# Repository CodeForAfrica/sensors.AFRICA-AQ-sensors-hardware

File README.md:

# AQ-Sensors-Hardware-Design

These are the design files for the https://sensors.africa/ by https://codeforafrica.org/ AQ kits PCB.

## Tools used

* Autodesk Eagle

* Fusion360

## sensors.AFRICA Stack

1. Firmware - https://github.com/CodeForAfrica/sensors.AFRICA-AQ-sensors-software

2. API - https://github.com/CodeForAfricaLabs/sensors.AFRICA-AQ-api

3. Map - https://github.com/CodeForAfrica/sensors.AFRICA-AQ-map-v2

## Documentation

The Documentation is under development.

## Attribution;

We used the following reference designs in our final design files. We are thankful to the owners for making them open-source.

1. https://github.com/adafruit/Adafruit-FONA-808-Breakout-PCB

2. https://github.com/SeaSlugLabs/Wisol-WSSFM10R2-Sigfox-Breakout/tree/master/Hardware

3. https://github.com/lupyuen/Wisol-WSSFM10R-Sigfox-Breakout

## License

GNU General Public License v3.0

sensors.AFRICA is a citizen-science focused project by Code for Africa that seeks to address data gaps by providing low cost sensors, which people can use to measure and monitor the quality of the air, water, and environment in their communities. This web app seeks to be the public portal through which most users would discover and explore the data and intiative.

Copyright (C) 2019 Code for Africa

This program is free software: you can redistribute it and/or modify
it under the terms of the GNU General Public License as published by
the Free Software Foundation, either version 3 of the License, or
(at your option) any later version.

This program is distributed in the hope that it will be useful,
but WITHOUT ANY WARRANTY; without even the implied warranty of
MERCHANTABILITY or FITNESS FOR A PARTICULAR PURPOSE. See the
GNU General Public License for more details.

You should have received a copy of the GNU General Public License
along with this program. If not, see <https://www.gnu.org/licenses/>

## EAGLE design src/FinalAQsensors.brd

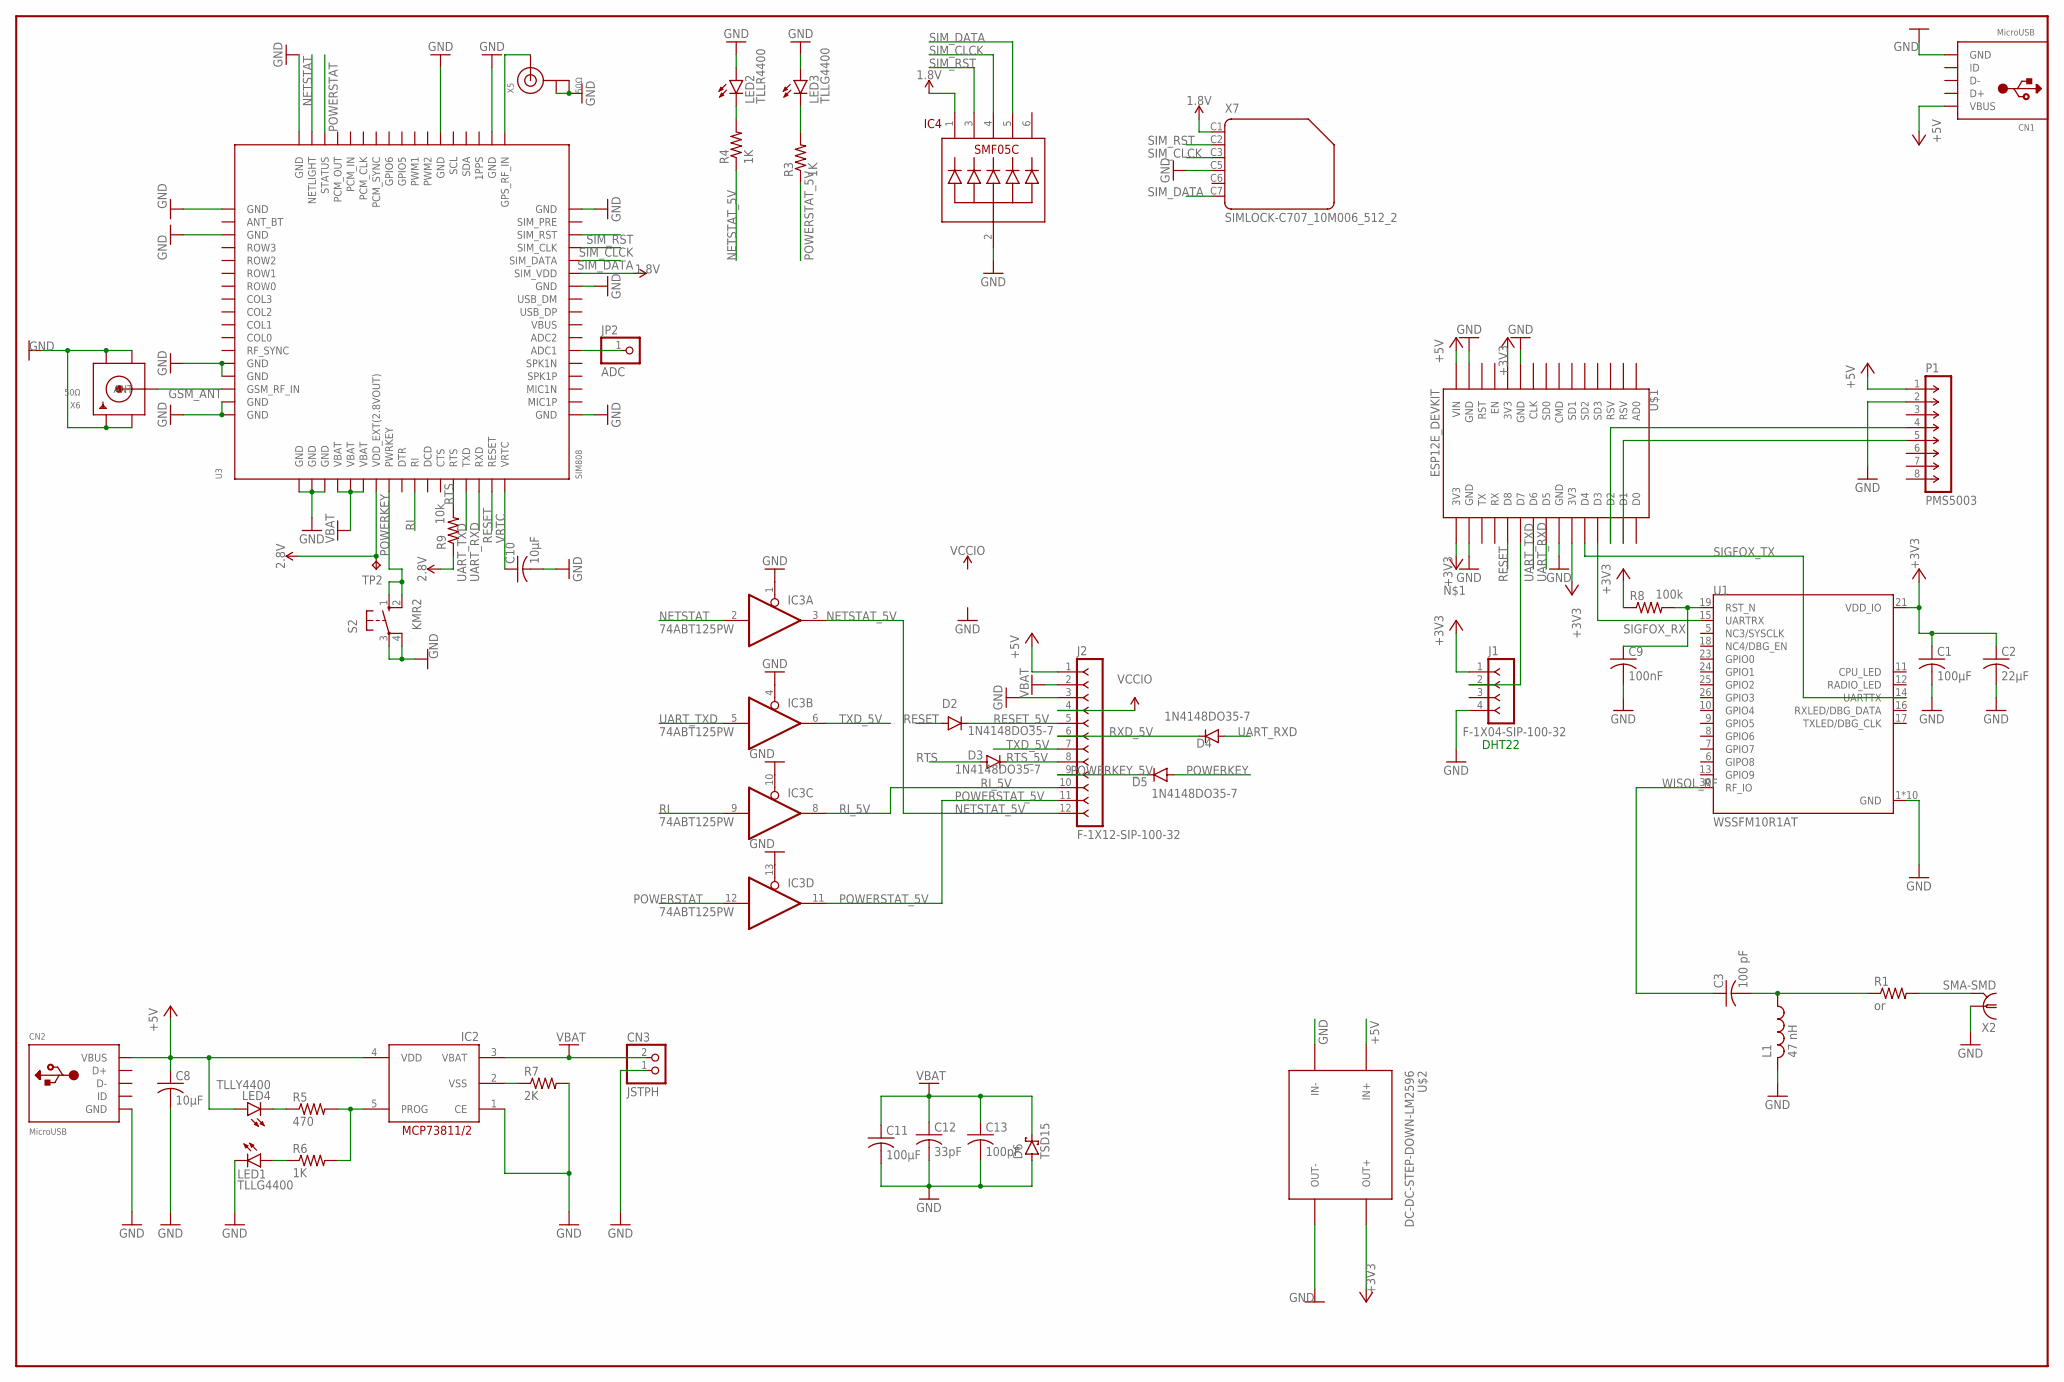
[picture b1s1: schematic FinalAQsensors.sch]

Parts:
C1: 100μF; C0201
C2: 22μF; C0201
C3: 100 pF; C0201
C8: 10μF; C025-025X050
C9: 100nF; C025-025X050
C10: 10μF; C0402
C11: 100μF; C0402
C12: 33pF; C0402
C13: 100pF; C0402
CN1, CN2: MicroUSB; USB-MINIB
CN3: JSTPH; JST-PH-2-SMT
D2, D3, D4, D5: 1N4148DO35-7; DO35-7
D6: TSD15; CB429-15
IC2: MCP73811/2; SOT23-5L
IC3: 74ABT125PW; TSSOP14
IC4: SMF05C; SC-70-6
J1: F-1X04-SIP-100-32; SIP-100-04-32
J2: F-1X12-SIP-100-32; SIP-100-12-32
JP2: ADC; 1X01M
L1: 47 nH; 0204/7
LED1, LED3: TLLG4400; LED3MM
LED2: TLLR4400; LED3MM
LED4: TLLY4400; LED3MM
P1: PMS5003; SIP-100-08-40
R1: or; 0204/5
R3, R4, R6: 1K; 0204/5
R5: 470; 0204/5
R7: 2K; 0204/5
R8: 100k; 0204/7
R9: 10k; 0204/5
S2: KMR2; B3F/40XX
TP2: TPTP10R; TP10R
U1: WSSFM10R1AT; XCVR_WSSFM10R1AT
U3: SIM808; SIM900_SMT
U$1: ESP12E_DEVKIT
U$2: DC-DC-STEP-DOWN-LM2596
X2: SMA-SMD
X5: 50Ω; U.FL
X6: 50Ω; SMA_EDGELAUNCH_UFL
X7: SIMLOCK-C707_10M006_512_2; C707_10M006_512_2

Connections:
1.8V: IC4.1, U3.P$29 (SIM_VDD), X7.C1 (1)
2.8V: R9.1, TP2.TP, U3.P$7 (VDD_EXT(2.8VOUT))
+3V3: C1.1, C2.1, J1.1, R8.1, U1.21 (VDD_IO), U$1.3V3@0 (3V3), U$1.3V3@1 (3V3), U$1.3V3@2 (3V3), U$2.OUT+
+5V: C8.1, CN1.VBUS, CN2.VBUS, IC2.4 (VDD), J2.1, LED4.A, P1.1, U$1.VIN, U$2.IN+
GND: C1.2, C2.2, C8.2, C9.2, C10.2, C11.2, C12.2, C13.2, CN1.GND, CN2.GND, CN3.1 (2), D6.A, IC2.1 (CE), IC3.1 (OE), IC3.4 (OE), IC3.7 (GND), IC3.10 (OE), IC3.13 (OE), IC4.2, J1.4, J2.3, L1.2, LED1.K (C), LED2.A, LED3.A, P1.2, R7.2, S2.3, S2.4 (P1), U1.1 (GND), U1.2 (GND), U1.3 (GND), U1.4 (GND), U1.20 (GND), U1.22 (GND), U1.27 (GND), U1.28 (GND), U1.29 (GND), U1.31 (GND), U3.P$1 (GND), U3.P$2 (GND), U3.P$3 (GND), U3.P$18 (GND), U3.P$28 (GND), U3.P$34 (GND), U3.P$36 (GND), U3.P$40 (GND), U3.P$51 (GND), U3.P$52 (GND), U3.P$54 (GND), U3.P$64 (GND), U3.P$65 (GND), U3.P$67 (GND), U3.P$68 (GND), U$1.GND@0 (GND), U$1.GND@1 (GND), U$1.GND@2 (GND), U$1.GND@3 (GND), U$2.IN-, U$2.OUT-, X2.1, X5.1 (GND), X5.2 (GND), X6.GND@1 (GND1), X6.GND@2 (GND2), X6.GND@3 (GND3), X6.GND@4 (GND4), X7.C5 (4)
GSM_ANT: U3.P$66 (GSM_RF_IN), X6.P (ANT)
unnamed: J1.2, U$1.D7
unnamed: C9.1, R8.2, U1.19 (RST_N)
unnamed: P1.4, U$1.D2
unnamed: P1.5, U$1.D1
unnamed: C3.2, L1.1, R1.1
unnamed: U3.P$35 (GPS_RF_IN), X5.3 (SIGNAL)
unnamed: R1.2, X2.2@1 (2), X2.2@2 (2), X2.2@3 (2), X2.2@4 (2), X2.2@5 (2), X2.2@6 (2)
unnamed: JP2.1, U3.P$23 (ADC1)
unnamed: LED2.K (C), R4.2
unnamed: LED3.K (C), R3.2
unnamed: LED4.K (C), R5.1
unnamed: IC2.5 (PROG), R5.2, R6.2
unnamed: LED1.A, R6.1
NETSTAT: IC3.2 (I), U3.P$50 (NETLIGHT)
NETSTAT_5V: IC3.3 (O), J2.12, R4.1
POWERKEY: D5.A, S2.1 (S), S2.2 (S1), U3.P$8 (PWRKEY)
POWERKEY_5V: D5.C, J2.9
POWERSTAT: IC3.12 (I), U3.P$49 (STATUS)
POWERSTAT_5V: IC3.11 (O), J2.11, R3.1
RESET: D2.A, U3.P$16 (RESET), U$1.D8
RESET_5V: D2.C, J2.5
RI: IC3.9 (I), U3.P$10 (RI)
RI_5V: IC3.8 (O), J2.10
RTS: D3.A, R9.2, U3.P$13 (RTS)
RTS_5V: D3.C, J2.8
RXD_5V: D4.C, J2.6
SIGFOX_RX: U1.15 (UARTRX), U$1.D3
SIGFOX_TX: U1.14 (UARTTX), U$1.D4
SIM_CLCK: IC4.4, U3.P$31 (SIM_CLK), X7.C3 (3)
SIM_DATA: IC4.5, U3.P$30 (SIM_DATA), X7.C7 (6)
SIM_RST: IC4.3, U3.P$32 (SIM_RST), X7.C2 (2)
TXD_5V: IC3.6 (O), J2.7
UART_RXD: D4.A, U3.P$15 (RXD), U$1.D5
UART_TXD: IC3.5 (I), U3.P$14 (TXD), U$1.D6
VBAT: C11.1, C12.1, C13.1, CN3.2 (1), D6.C, IC2.3 (VBAT), J2.2, U3.P$4 (VBAT), U3.P$5 (VBAT), U3.P$6 (VBAT)
VBUS: U3.P$25 (VBUS)
VCC: IC3.14 (VCC)
VCCIO: J2.4
VRTC: C10.1, U3.P$17 (VRTC)
VSS: IC2.2 (VSS), R7.1
WISOL_RF: C3.1, U1.30 (RF_IO)

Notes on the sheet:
DHT22

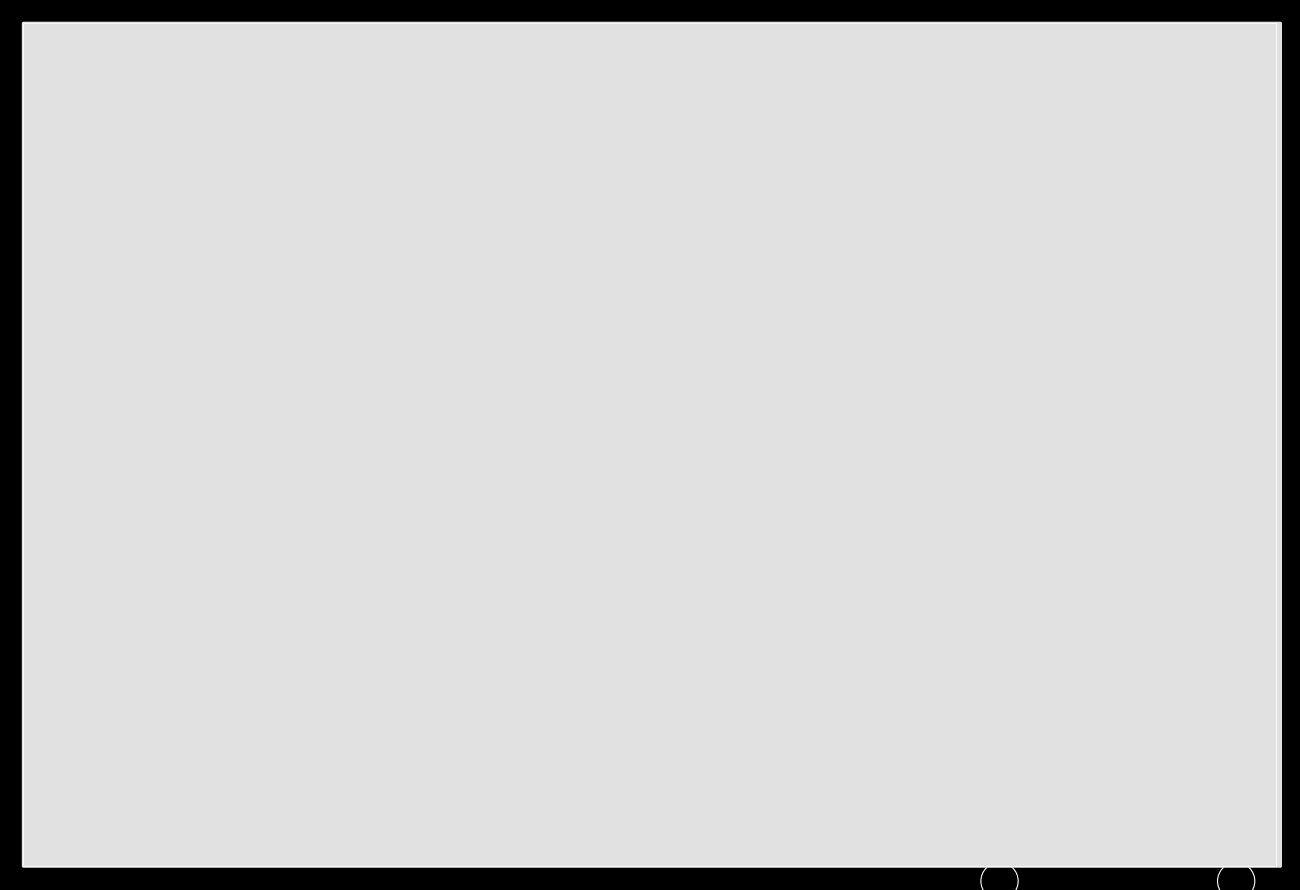
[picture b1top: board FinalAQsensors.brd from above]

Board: 2 copper layers, 107.6 x 72.4 mm, 47 parts (0 on the bottom side), 44 nets.

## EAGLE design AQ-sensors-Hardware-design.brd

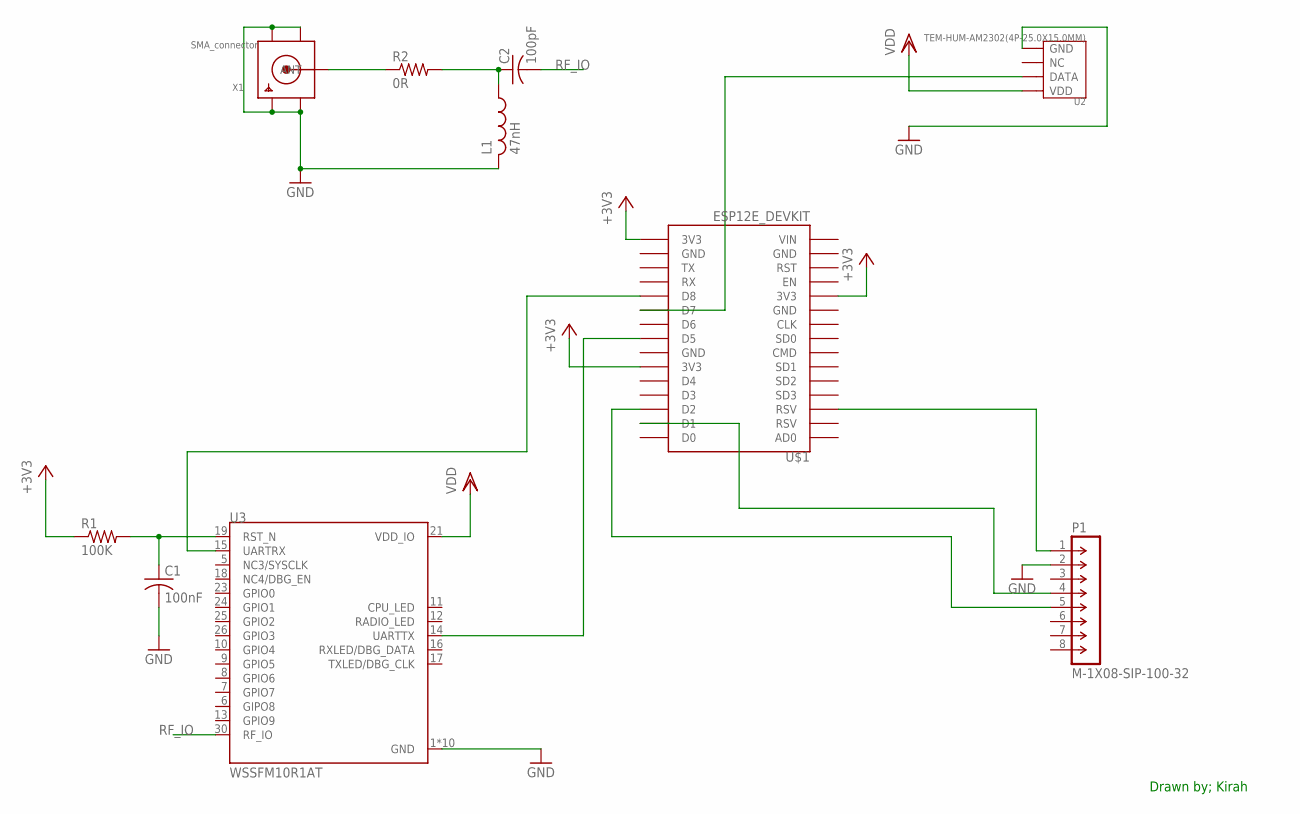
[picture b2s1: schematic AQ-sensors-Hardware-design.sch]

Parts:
C1: 100nF; C025-025X050
C2: 100pF; C025-025X050
L1: 47nH; 0204/7
P1: M-1X08-SIP-100-32; SIP-100-08-32
R1: 100K; 0204/7
R2: 0R; 0204/7
U2: TEM-HUM-AM2302(4P-25.0X15.0MM); SNR4-2.54-25.0X15.0X7.0MM
U3: WSSFM10R1AT; XCVR_WSSFM10R1AT
U$1: ESP12E_DEVKIT
X1: SMA_connector; SMA_EDGELAUNCH_UFL

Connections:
+3V3: R1.1, U$1.3V3@0 (3V3), U$1.3V3@1 (3V3), U$1.3V3@2 (3V3)
GND: C1.2, L1.2, P1.2, U2.P$4 (GND), U3.1 (GND), U3.2 (GND), U3.3 (GND), U3.4 (GND), U3.20 (GND), U3.22 (GND), U3.27 (GND), U3.28 (GND), U3.29 (GND), U3.31 (GND), X1.GND@1 (GND1), X1.GND@2 (GND2), X1.GND@3 (GND3), X1.GND@4 (GND4)
unnamed: U2.P$2 (DATA), U$1.D7
unnamed: C1.1, R1.2, U3.19 (RST_N)
unnamed: C2.1, L1.1, R2.2
unnamed: P1.1, U$1.RSV@1 (RSV)
unnamed: R2.1, X1.P (ANT)
unnamed: U3.15 (UARTRX), U$1.D8
unnamed: U3.14 (UARTTX), U$1.D5
unnamed: P1.5, U$1.D2
unnamed: P1.4, U$1.D1
RF_IO: C2.2, U3.30 (RF_IO)
VDD: U2.P$1 (VDD), U3.21 (VDD_IO)

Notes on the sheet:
Drawn by; Kirah

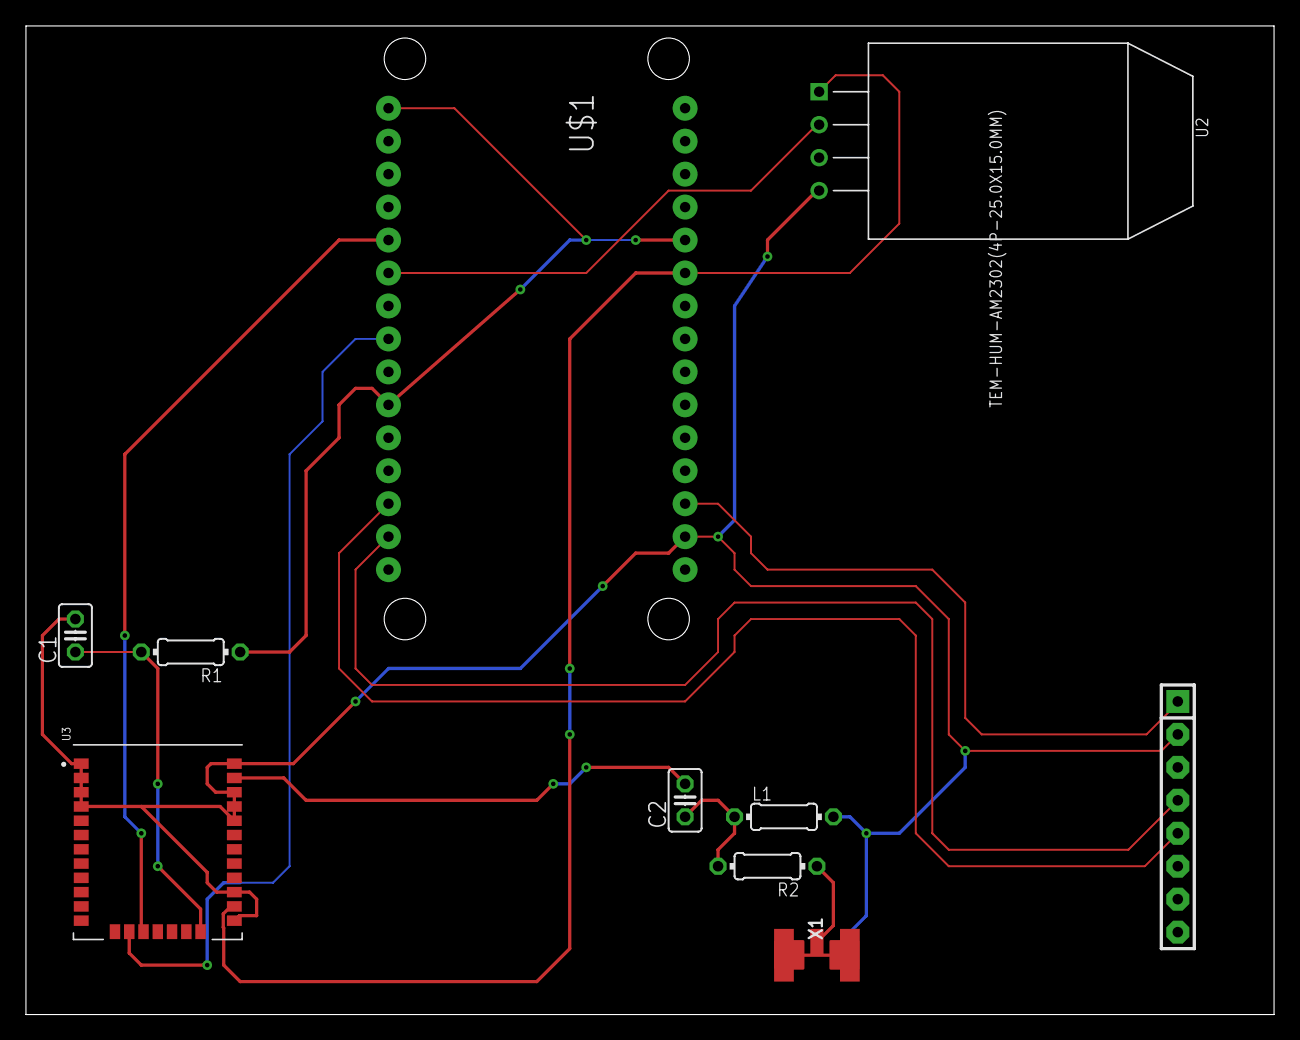
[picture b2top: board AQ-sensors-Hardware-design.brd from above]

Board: 2 copper layers, 96.2 x 76.2 mm, 10 parts (0 on the bottom side), 13 nets.

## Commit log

2019-06-04 Revert "Add files via upload"
2020-02-18 Create .github
    PR template.
2020-03-17 Create .github
    PR Template
2020-03-17 Rename .github to PR Template
    PULL_REQUEST_TEMPLATE.md
2020-03-17 Rename PR Template to .github/PR Template
2020-03-17 Rename FinalAQsensors.brd to .src/FinalAQsensors.brd
2020-03-17 Rename FinalAQsensors.sch to src/FinalAQsensors.sch
2020-03-17 Revert "Rename PR Template to .github/PR Template"
    This reverts commit fd4cc50b5b9b980397702522e110659ee212ffc6.
2020-03-17 Revert "Rename FinalAQsensors.brd to .src/FinalAQsensors.brd"
    This reverts commit 5ddb4b9306e111e8f3574c48de849e74efe17024.
2020-03-17 Rename FinalAQsensors.brd to src/FinalAQsensors.brd
2020-03-18 Create LICENSE

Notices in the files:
parts and their libraries:
con-headers-jp: Copyright (C) 2008, Bob Starr
supply0: Copyright (C) 2007, Bob Starr
SparkFun-PowerSymbols: Licensing: Creative Commons ShareAlike 4.0 International - https://creativecommons.org/licenses/by-sa/4.0
